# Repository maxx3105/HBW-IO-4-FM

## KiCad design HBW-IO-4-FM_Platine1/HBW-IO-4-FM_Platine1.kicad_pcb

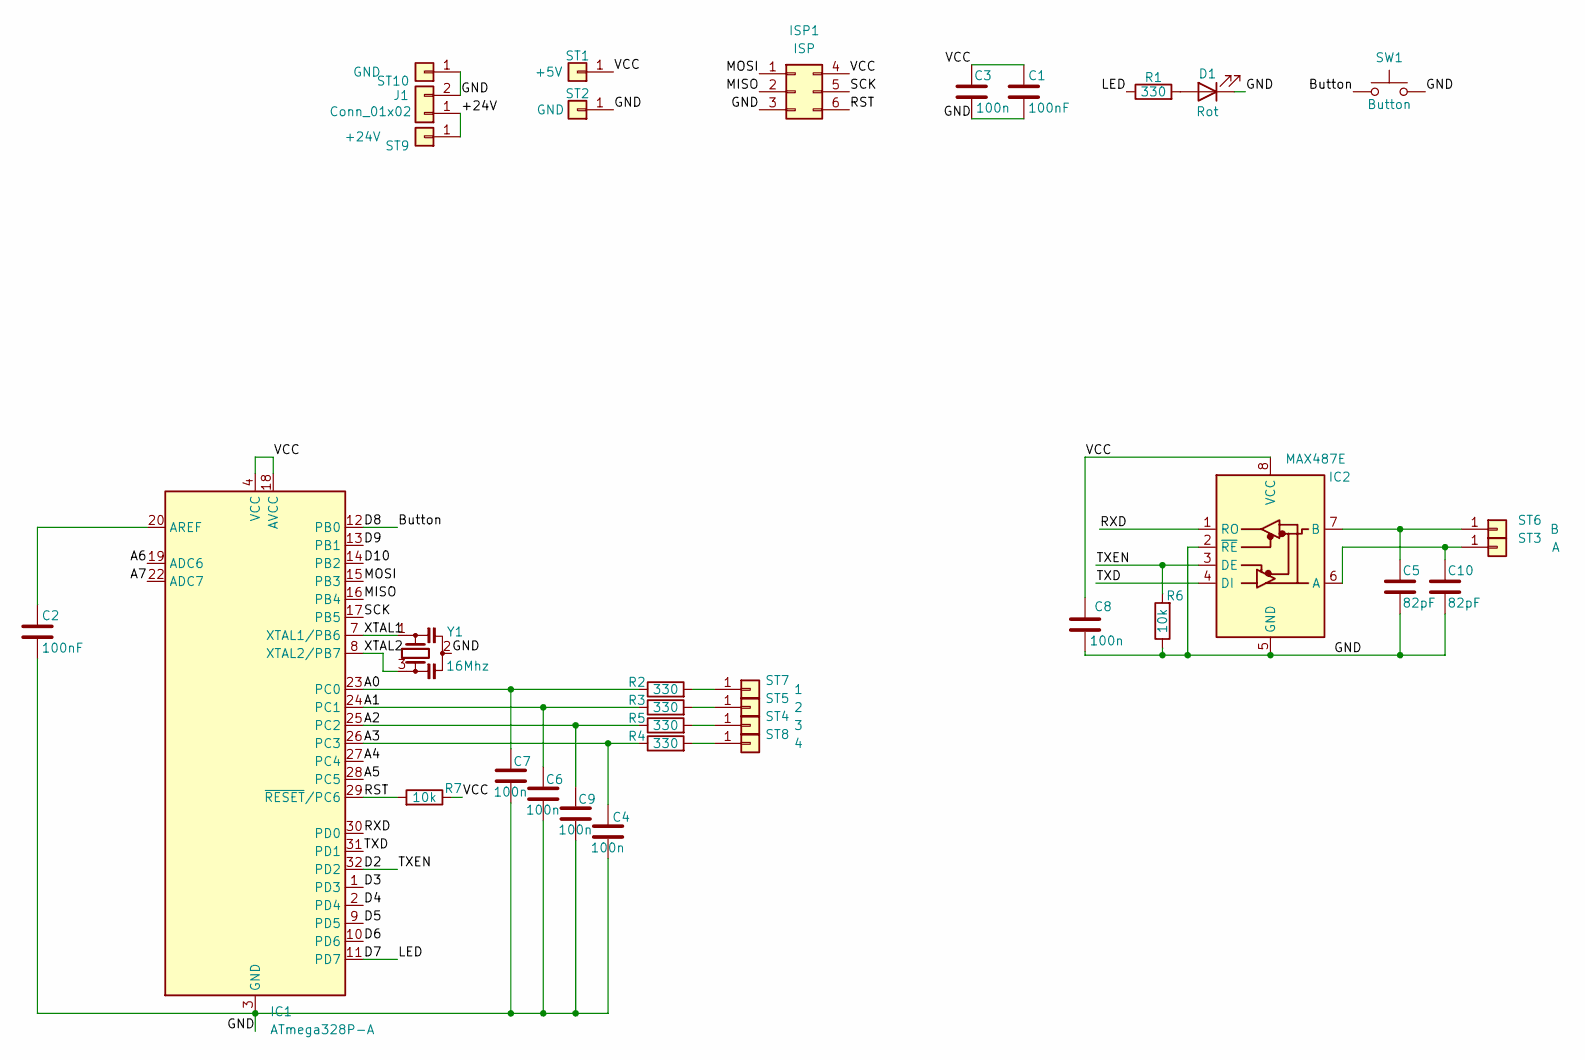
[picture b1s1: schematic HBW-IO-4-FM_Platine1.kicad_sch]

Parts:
C1, C2: 100nF; C_0805_2012Metric_Pad1.18x1.45mm_HandSolder
C3, C4, C6, C7, C8, C9: 100n; C_0805_2012Metric_Pad1.18x1.45mm_HandSolder
C5, C10: 82pF; C_0805_2012Metric_Pad1.18x1.45mm_HandSolder
D1: Rot; LED_D3.0mm
IC1: ATmega328P-A; TQFP-32_7x7mm_P0.8mm
IC2: MAX487E; SOIC-8_3.9x4.9mm_P1.27mm
ISP1: ISP; TestPoint_Homematic
J1: Conn_01x02; PinHeader_1x02_P2.54mm_Vertical
R1, R2, R3, R4, R5: 330; R_0805_2012Metric_Pad1.20x1.40mm_HandSolder
R6, R7: 10k; R_0805_2012Metric_Pad1.20x1.40mm_HandSolder
ST1: +5V; TestPoint_THTPad_2.0x2.0mm_Drill1.0mm
ST2: GND; TestPoint_THTPad_2.0x2.0mm_Drill1.0mm
ST3: A; TestPoint_Pad_2.0x1.0mm
ST4: 3; TestPoint_Pad_2.0x1.0mm
ST5: 2; TestPoint_Pad_2.0x1.0mm
ST6: B; TestPoint_Pad_2.0x1.0mm
ST7: 1; TestPoint_Pad_2.0x1.0mm
ST8: 4; TestPoint_Pad_2.0x1.0mm
ST9: +24V; TestPoint_Pad_2.0x1.0mm
ST10: GND; TestPoint_Pad_2.0x1.0mm
SW1: Button; SW_Push_1P1T_NO_CK_KMR2
Y1: 16Mhz; Resonator_SMD_Murata_CSTxExxV-3Pin_3.0x1.1mm

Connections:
/+24V: J1.1, ST9.1
/A0: C7.1, IC1.23 (PC0), R2.1
/A1: C6.1, IC1.24 (PC1), R3.1
/A2: C9.1, IC1.25 (PC2), R5.1
/A3: C4.1, IC1.26 (PC3), R4.1
/A4: IC1.27 (PC4)
/A5: IC1.28 (PC5)
/A6: IC1.19 (ADC6)
/A7: IC1.22 (ADC7)
/Button: IC1.12 (PB0), SW1.1
/D2: IC1.32 (PD2), IC2.3 (DE), R6.2
/D3: IC1.1 (PD3)
/D4: IC1.2 (PD4)
/D5: IC1.9 (PD5)
/D6: IC1.10 (PD6)
/D7: IC1.11 (PD7), R1.1
/D9: IC1.13 (PB1)
/D10: IC1.14 (PB2)
/GND: C1.1, C2.1, C3.2, C4.2, C5.2, C6.2, C7.2, C8.1, C9.2, C10.2, D1.1 (K), IC1.3 (GND), IC1.5 (GND), IC1.21 (GND), IC2.2 (~RE), IC2.5 (GND), ISP1.3, J1.2, R6.1, ST2.1, ST10.1, SW1.2, Y1.2; also elsewhere on the board
/MISO: IC1.16 (PB4), ISP1.2; also elsewhere on the board
/MOSI: IC1.15 (PB3), ISP1.1; also elsewhere on the board
/RST: IC1.29 (~RESET/PC6), ISP1.6, R7.2; also elsewhere on the board
/RXD: IC1.30 (PD0), IC2.1 (RO)
/SCK: IC1.17 (PB5), ISP1.5; also elsewhere on the board
/TXD: IC1.31 (PD1), IC2.4 (DI)
/VCC: C1.2, C3.1, C8.2, IC1.4 (VCC), IC1.6 (VCC), IC1.18 (AVCC), IC2.8 (VCC), ISP1.4, R7.1, ST1.1; also elsewhere on the board
/XTAL1: IC1.7 (XTAL1/PB6), Y1.1
/XTAL2: IC1.8 (XTAL2/PB7), Y1.3
unnamed: C2.2, IC1.20 (AREF)
unnamed: C5.1, IC2.7 (B), ST6.1
unnamed: C10.1, IC2.6 (A), ST3.1
unnamed: D1.2 (A), R1.2
unnamed: R2.2, ST7.1
unnamed: R3.2, ST5.1
unnamed: R5.2, ST4.1
unnamed: R4.2, ST8.1

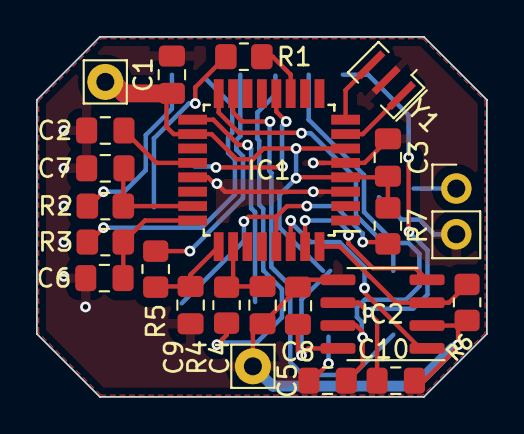
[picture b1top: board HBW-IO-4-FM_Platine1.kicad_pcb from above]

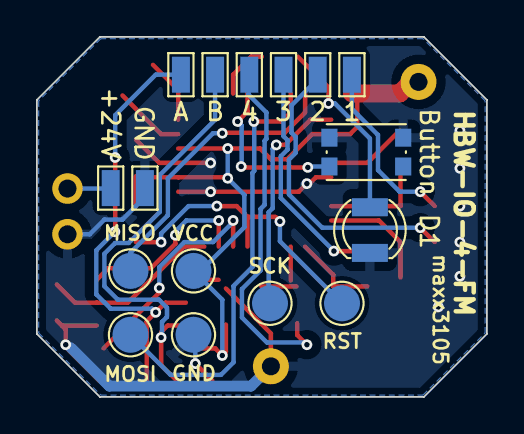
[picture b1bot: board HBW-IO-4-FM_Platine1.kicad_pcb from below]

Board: 2 copper layers, 25.0 x 20.0 mm, 34 parts (11 on the bottom side), 26 nets.

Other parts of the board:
ISP: ISP; TestPoint_Homematic

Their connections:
/GND: ISP.3; also elsewhere on the board
/MISO: ISP.2; also elsewhere on the board
/MOSI: ISP.1; also elsewhere on the board
/RST: ISP.6; also elsewhere on the board
/SCK: ISP.5; also elsewhere on the board
/VCC: ISP.4; also elsewhere on the board

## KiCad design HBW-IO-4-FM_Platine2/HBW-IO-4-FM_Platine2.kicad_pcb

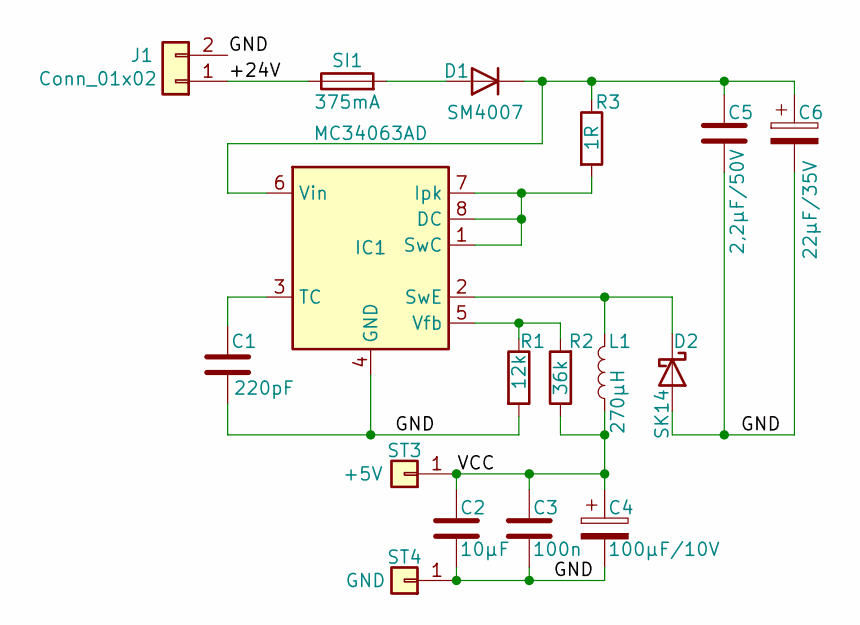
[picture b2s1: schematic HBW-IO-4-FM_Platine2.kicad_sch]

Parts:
C1: 220pF; C_0805_2012Metric_Pad1.18x1.45mm_HandSolder
C2: 10µF; C_1210_3225Metric_Pad1.33x2.70mm_HandSolder
C3: 100n; C_0805_2012Metric_Pad1.18x1.45mm_HandSolder
C4: 100µF/10V; CP_EIA-7343-20_Kemet-V_Pad2.25x2.55mm_HandSolder
C5: 2,2µF/50V; C_1210_3225Metric_Pad1.33x2.70mm_HandSolder
C6: 22µF/35V; CP_Elec_5x5.8
D1: SM4007; D_MELF
D2: SK14; D_SMA_Handsoldering
IC1: MC34063AD; SOIC-8_3.9x4.9mm_P1.27mm
J1: Conn_01x02; PinHeader_1x02_P2.54mm_Vertical
L1: 270µH; L_Taiyo-Yuden_MD-4040
R1: 12k; R_0805_2012Metric_Pad1.20x1.40mm_HandSolder
R2: 36k; R_0805_2012Metric_Pad1.20x1.40mm_HandSolder
R3: 1R; R_0805_2012Metric_Pad1.20x1.40mm_HandSolder
SI1: 375mA; FUSC6127X294N
ST3: +5V; TestPoint_THTPad_2.0x2.0mm_Drill1.0mm
ST4: GND; TestPoint_THTPad_2.0x2.0mm_Drill1.0mm

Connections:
/+24V: J1.1, SI1.1
/GND: C1.2, C2.2, C3.1, C4.2, C5.2, C6.2, D2.2 (A), IC1.4 (GND), J1.2, R1.2, ST4.1
/VCC: C2.1, C3.2, C4.1, L1.1, R2.1, ST3.1
unnamed: C1.1, IC1.3 (TC)
unnamed: C5.1, C6.1, D1.1 (K), IC1.6 (Vin), R3.1
unnamed: D1.2 (A), SI1.2
unnamed: D2.1 (K), IC1.2 (SwE), L1.2
unnamed: IC1.1 (SwC), IC1.7 (Ipk), IC1.8 (DC), R3.2
unnamed: IC1.5 (Vfb), R1.1, R2.2

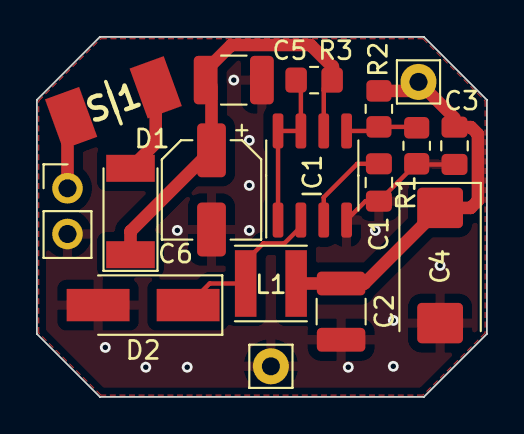
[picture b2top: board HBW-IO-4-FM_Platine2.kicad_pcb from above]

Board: 2 copper layers, 25.0 x 20.0 mm, 17 parts (0 on the bottom side), 9 nets.

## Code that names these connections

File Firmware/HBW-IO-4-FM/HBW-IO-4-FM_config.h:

/* Pin- und Hardware-Konfiguration für HBW-IO-4-FM
 *
 * Ziel-Hardware = maxx3105 "HBW-IO-4-FM" Platine1:
 *   - ATmega328P-A @ 16 MHz, 5 V
 *   - RS485-Transceiver MAX487E am HARDWARE-UART (Serial):
 *       RO -> PD0 (RX0),  DI -> PD1 (TX0),  DE+/RE -> PD2 (D2) = TXEN
 *   - 4 IOs je über 330 Ω an die Klemmen ST7/ST5/ST4/ST8:
 *       IO1 = A0 (PC0),  IO2 = A1 (PC1),  IO3 = A2 (PC2),  IO4 = A3 (PC3)
 *   - LED = D7 (PD7),  Config-Button = D8 (PB0)
 *   - Stromversorgung über Platine2 (MC34063AD-Buck 24 V -> 5 V)
 *
 * Pinquelle: HBW-IO-4-FM_Platine1.kicad_sch / .pdf (Repo maxx3105/HBW-IO-4-FM).
 *
 * RS485 liegt fest auf dem Hardware-UART -> KEIN serielles Debug verfügbar
 * (HBW_DEBUGSTREAM = NULL). Flashen per ISP (ISP1-Header) oder UART-Bootloader
 * bei abgezogenem Bus. MightyCore/Arduino-Clock: "16 MHz external".
 */

#ifndef HBW_IO_4_FM_CONFIG_H
#define HBW_IO_4_FM_CONFIG_H

#include <Arduino.h>
#include <EEPROM.h>
#include "FreeRam.h"

EEPROMClass* EepromPtr = &EEPROM;   // internes EEPROM

#if defined(__AVR_ATmega328P__) || defined(__AVR_ATmega328__)

  // 4 IOs an PC0..PC3 (= A0..A3), je 330 Ω in Reihe (siehe Schaltplan Platine1)
  #define IO1   A0      // PC0  -> ST7
  #define IO2   A1      // PC1  -> ST5
  #define IO3   A2      // PC2  -> ST4
  #define IO4   A3      // PC3  -> ST8

  #define LED         7     // PD7
  #define BUTTON      8     // PB0 (D8) -> Config-Taster gegen GND

  // RS485 auf dem Hardware-UART (RO->PD0/RX0, DI->PD1/TX0)
  #define RS485_TXEN  2         // PD2 (D2) -> MAX487 DE + /RE
  #define HBW_RS485       (Serial)
  #define HBW_DEBUGSTREAM (NULL)
  #define HBW_BEGIN_SERIALS() do { Serial.begin(19200, SERIAL_8E1); } while (0)

#else
  #error "HBW-IO-4-FM: Nicht unterstuetzter Mikrocontroller. Ziel ist ATmega328P (Platine1)."
#endif

#endif  // HBW_IO_4_FM_CONFIG_H
